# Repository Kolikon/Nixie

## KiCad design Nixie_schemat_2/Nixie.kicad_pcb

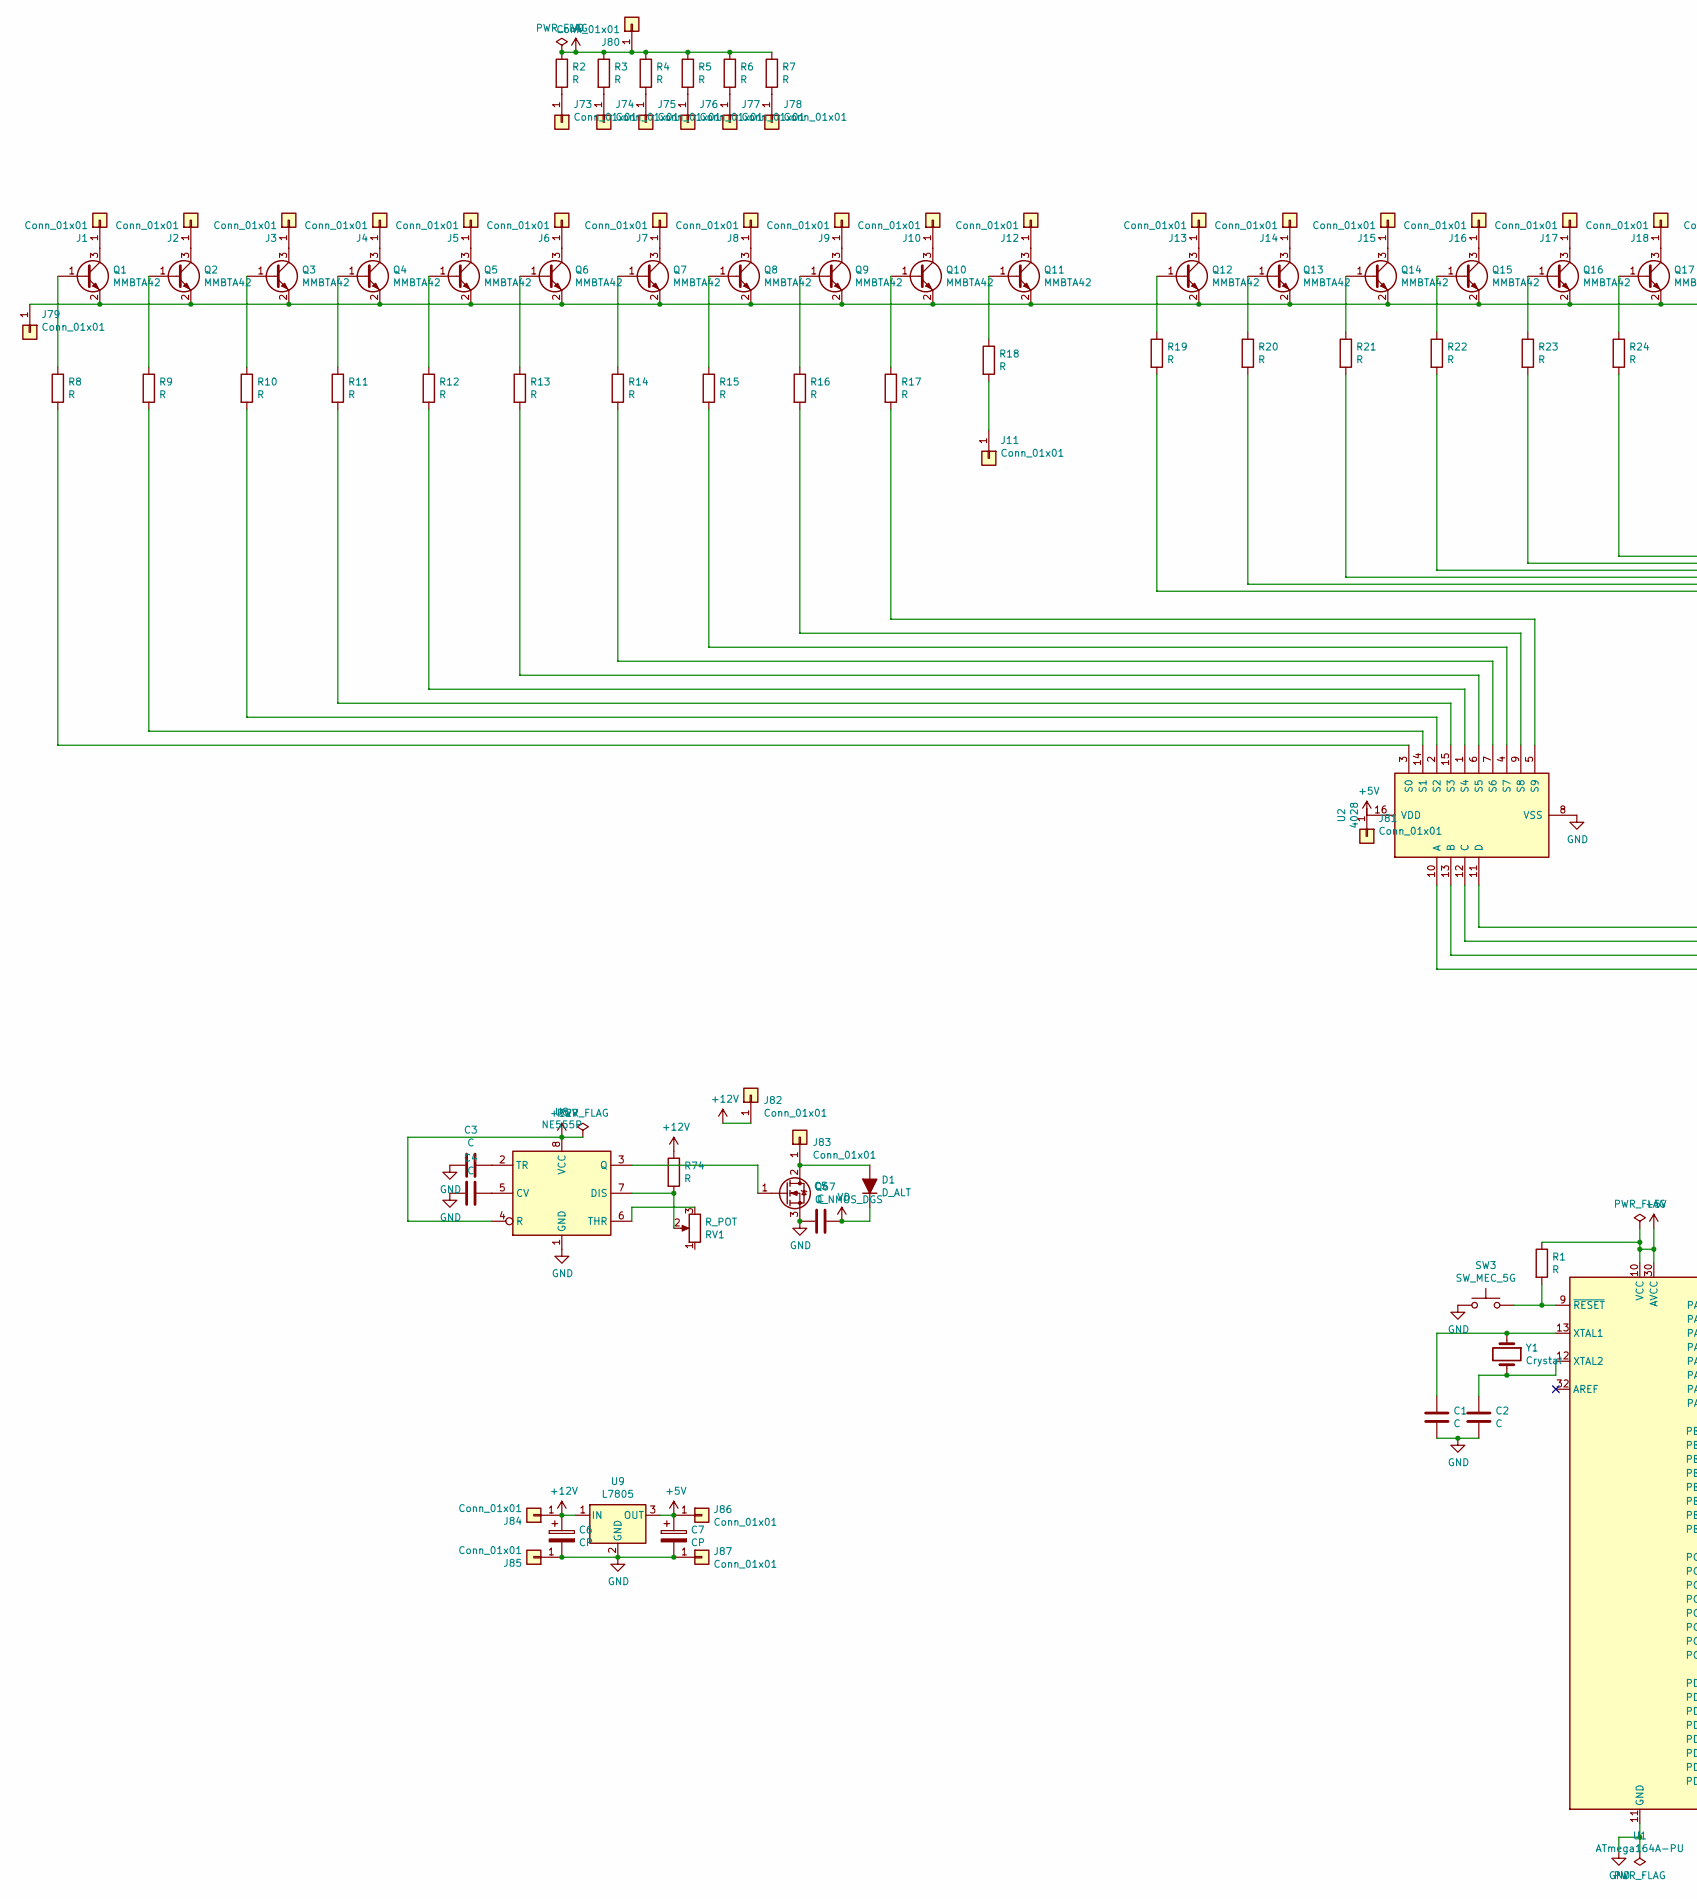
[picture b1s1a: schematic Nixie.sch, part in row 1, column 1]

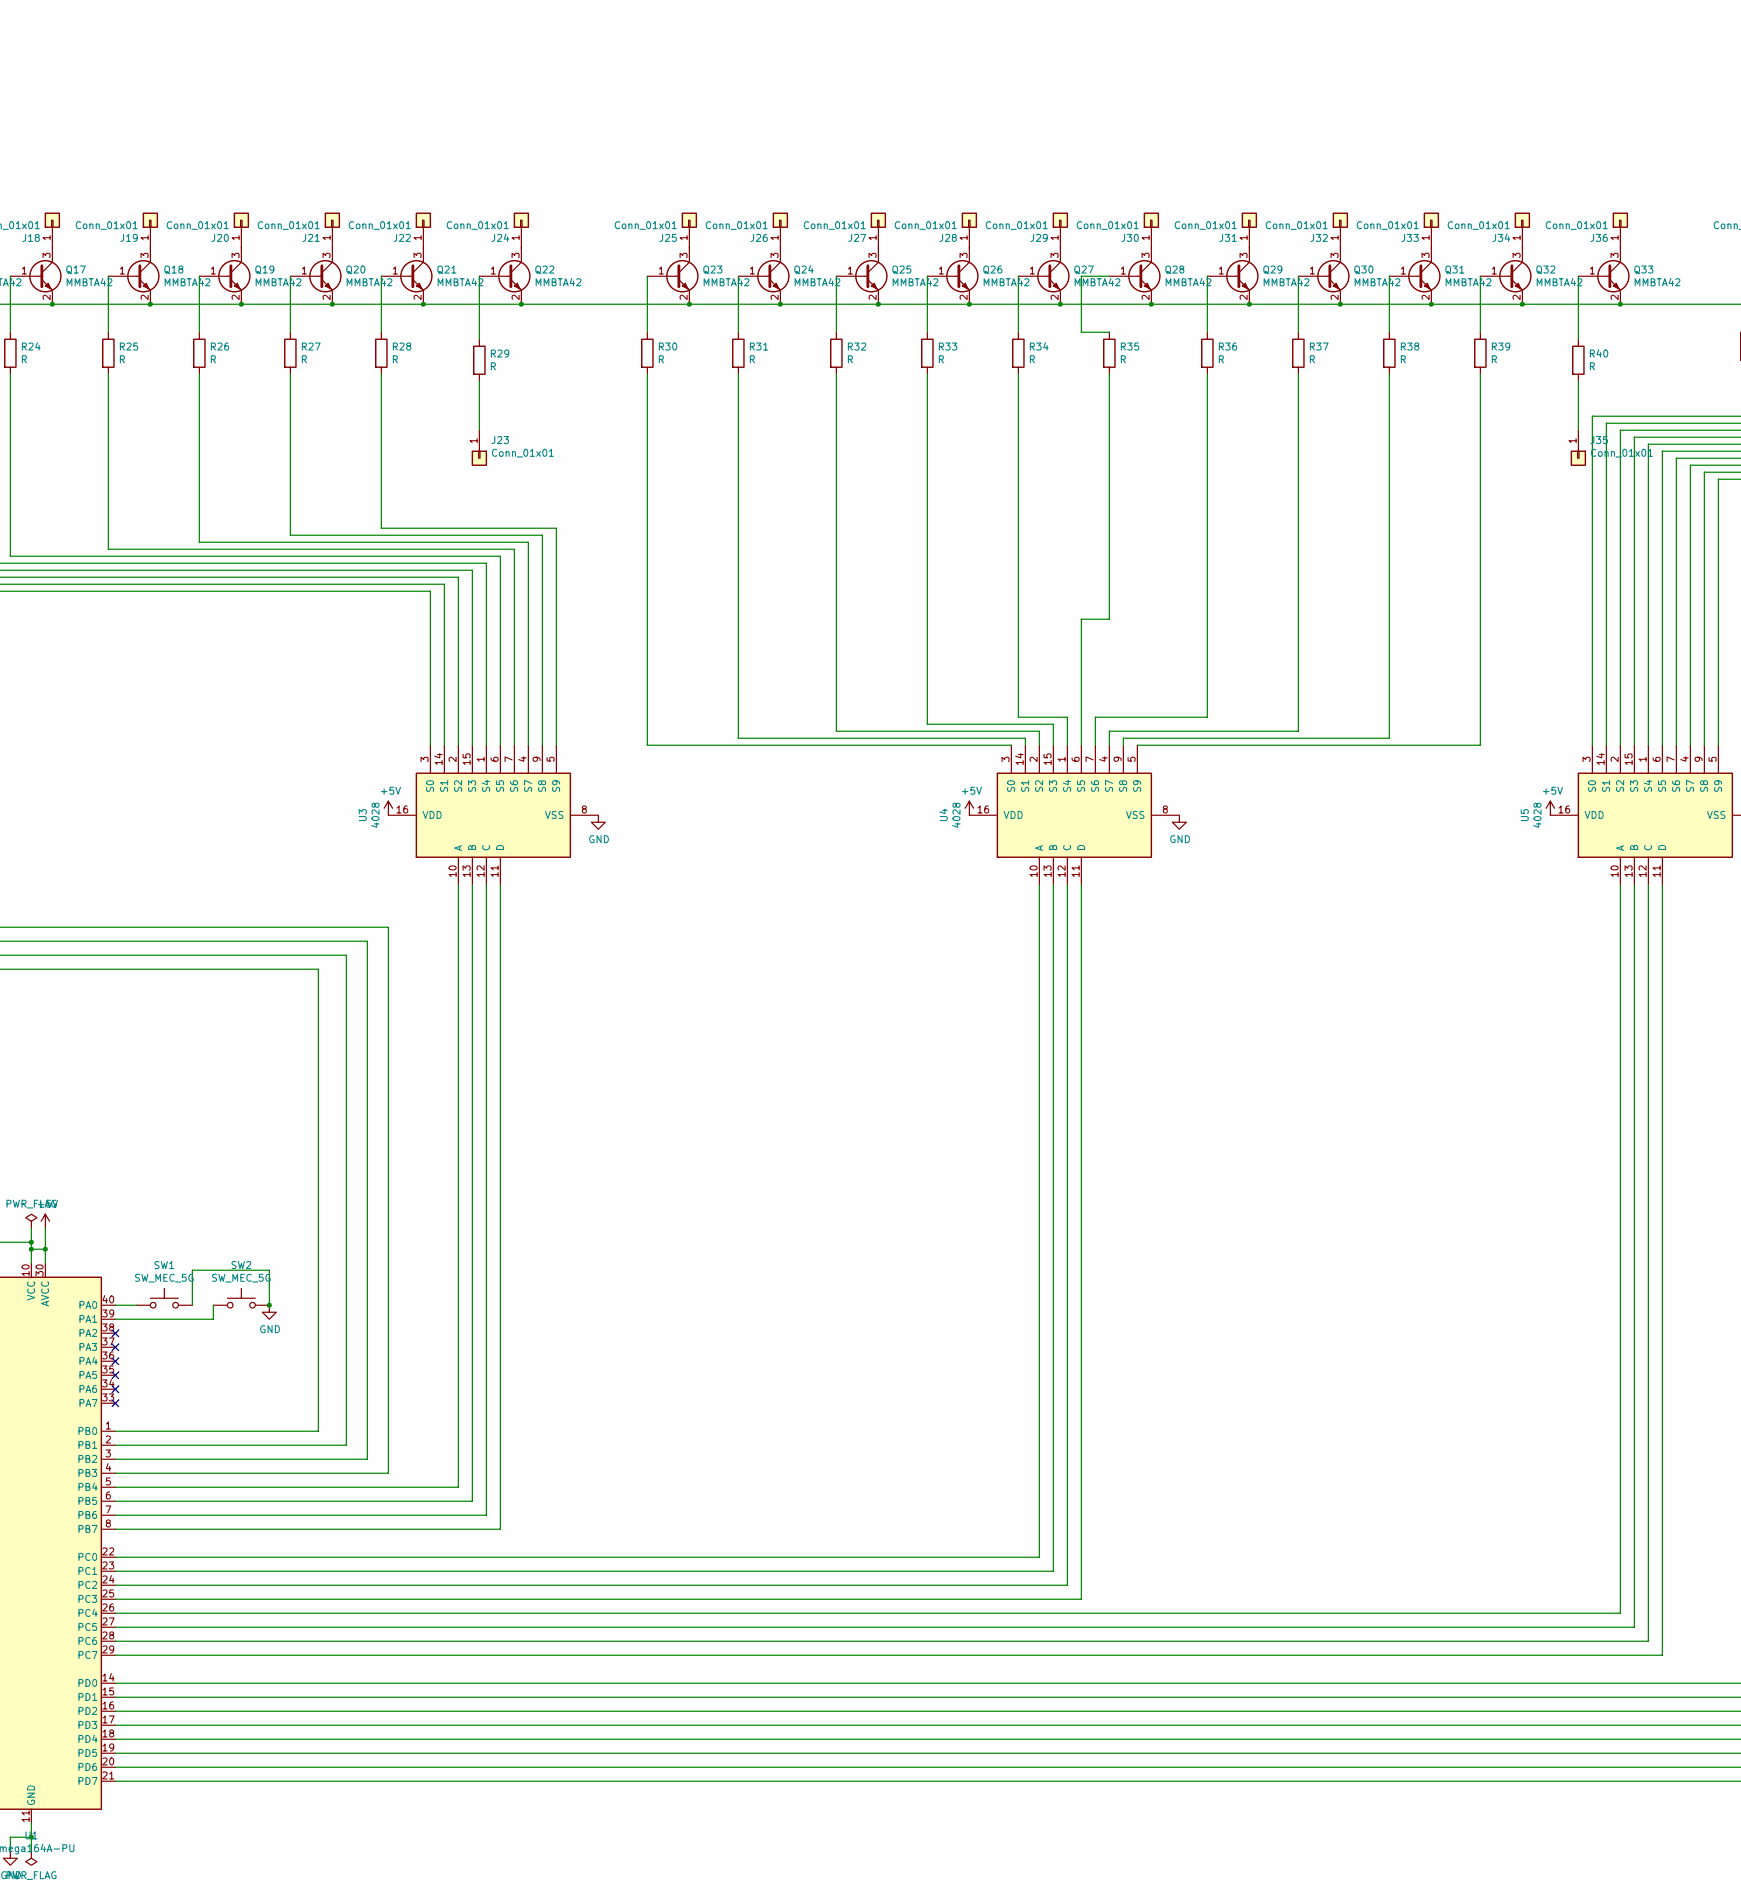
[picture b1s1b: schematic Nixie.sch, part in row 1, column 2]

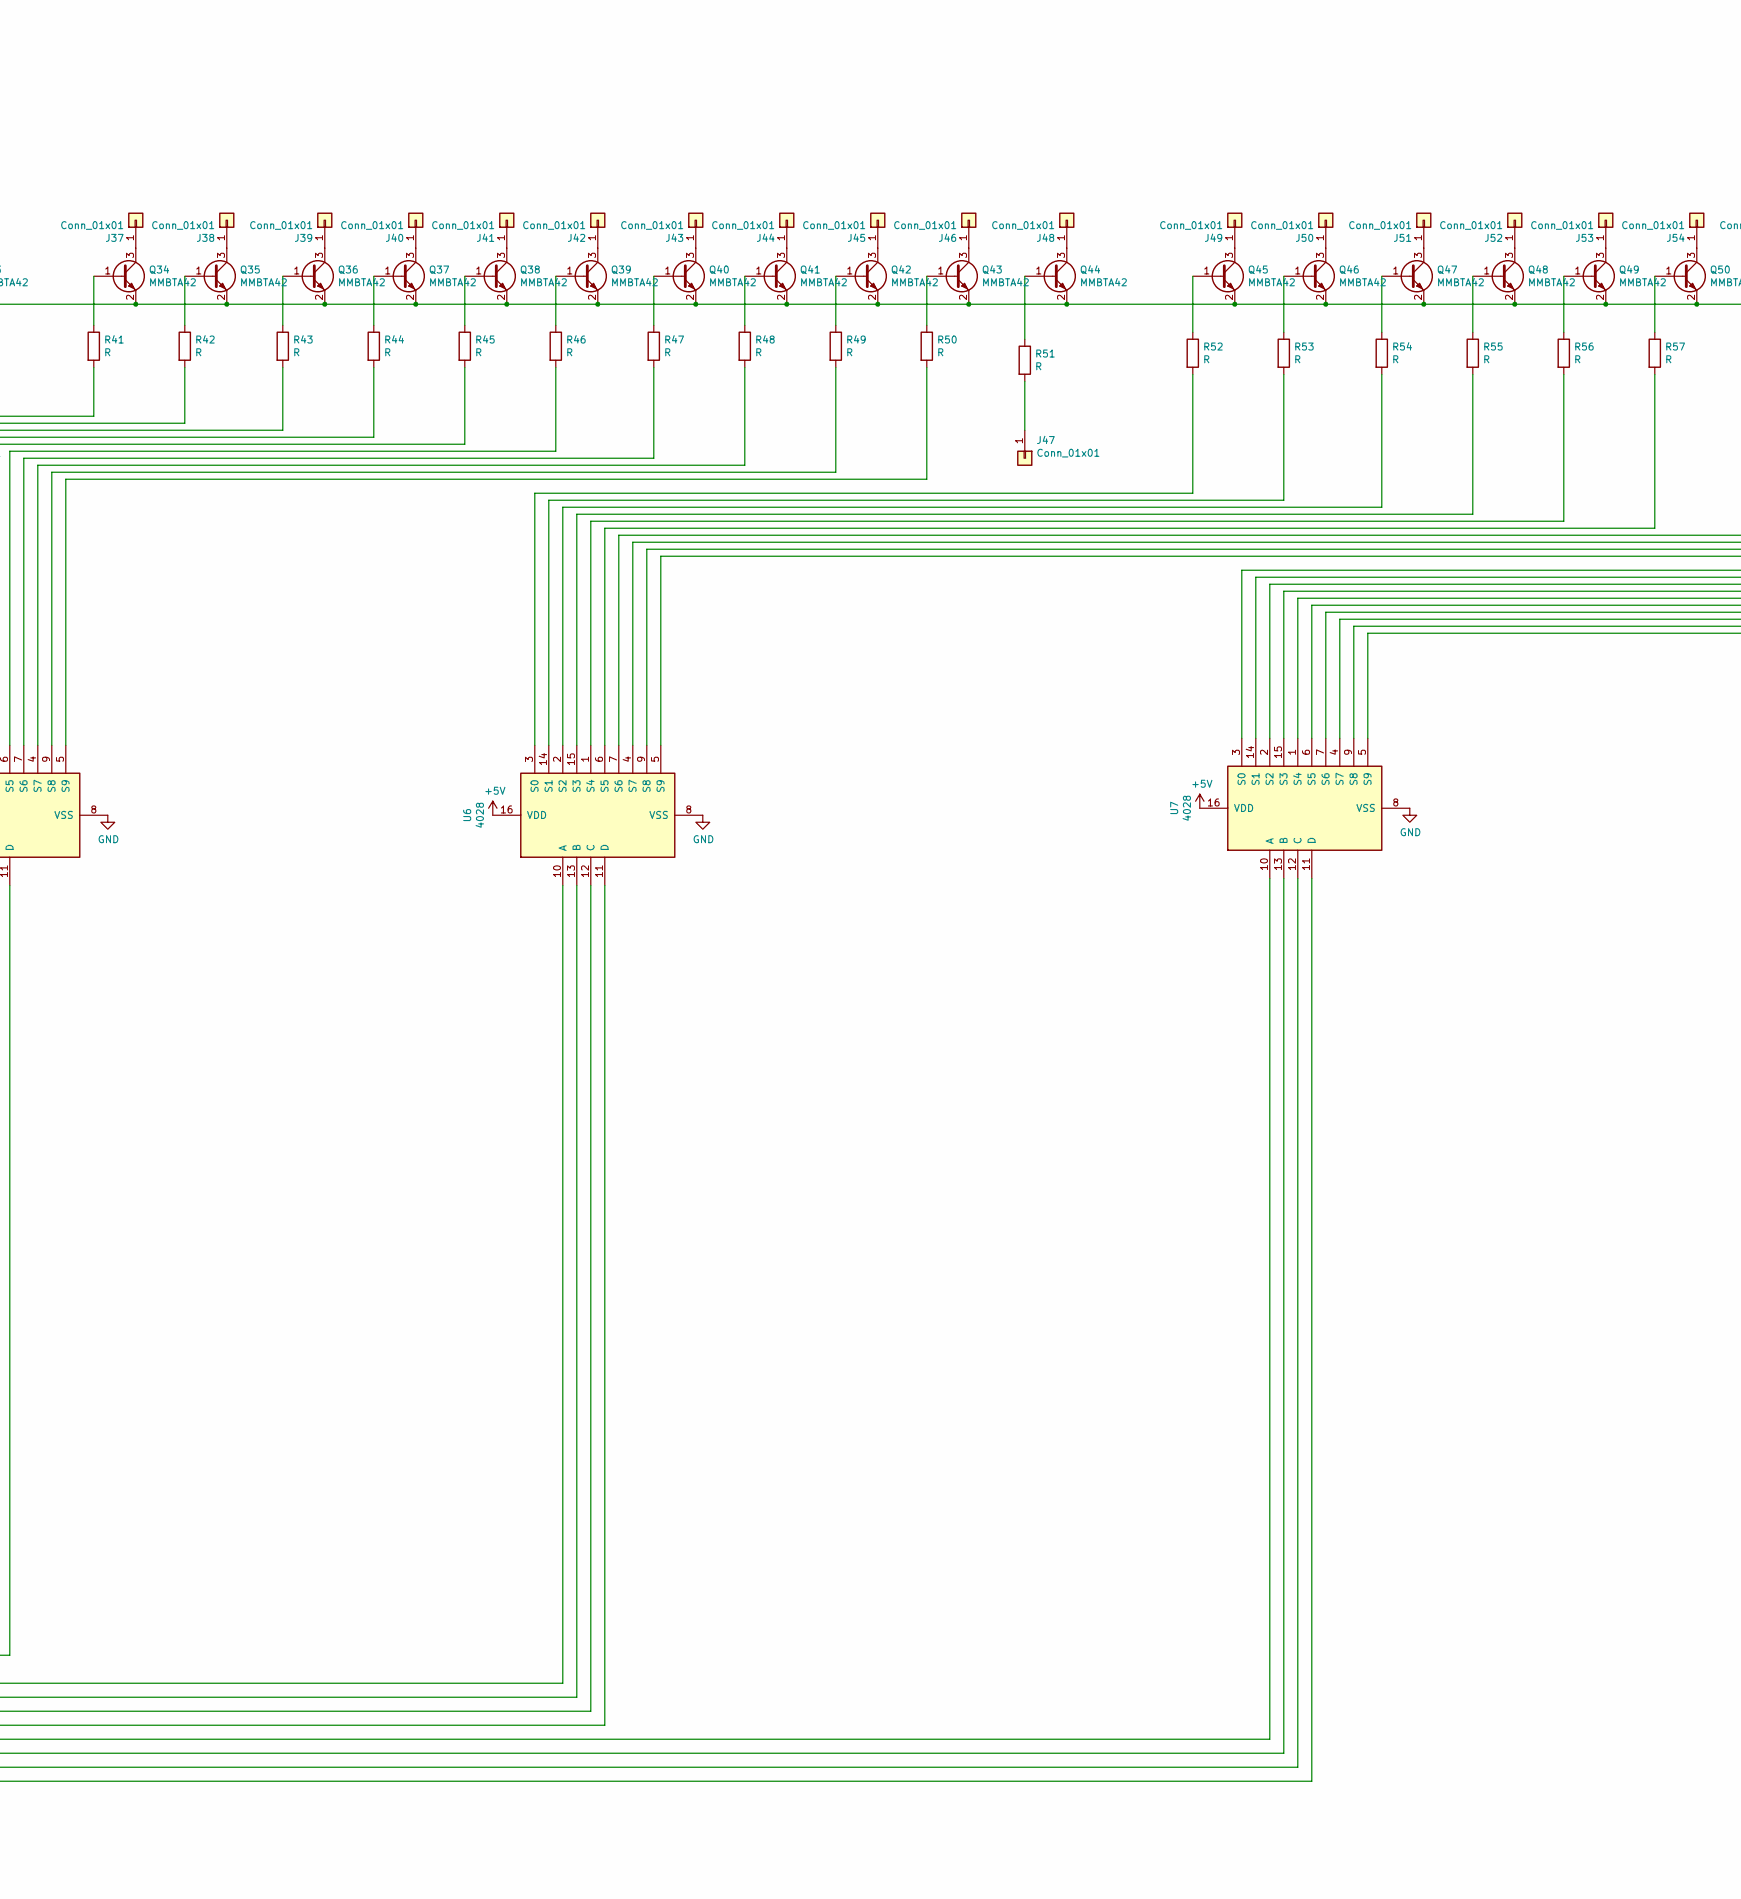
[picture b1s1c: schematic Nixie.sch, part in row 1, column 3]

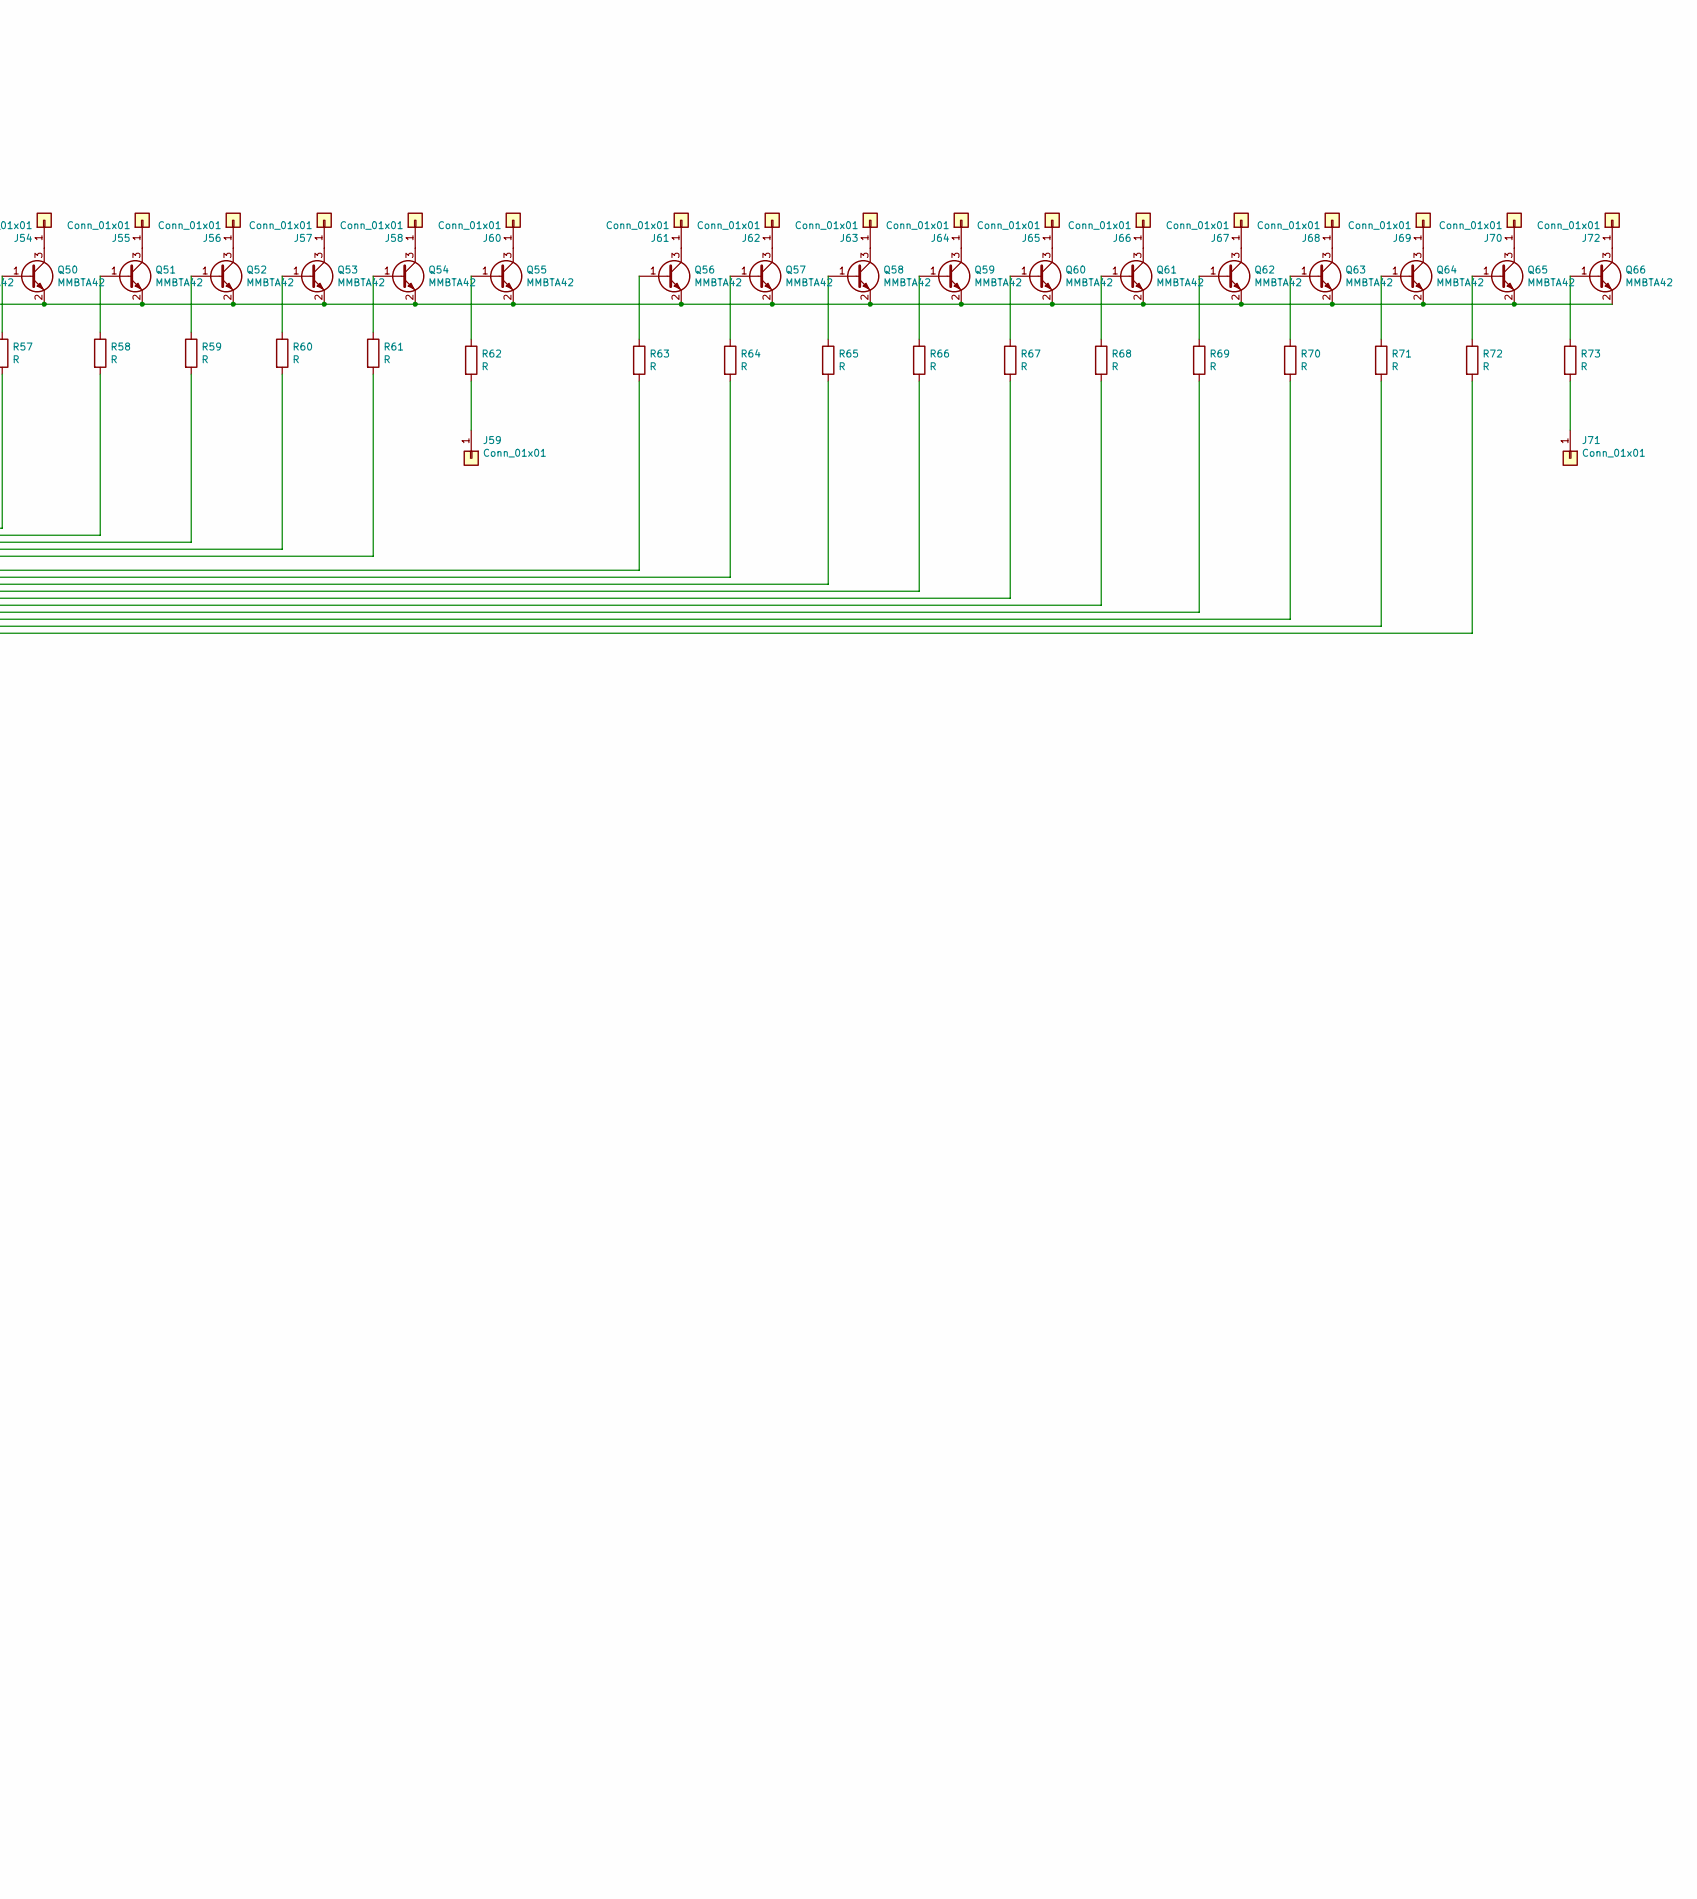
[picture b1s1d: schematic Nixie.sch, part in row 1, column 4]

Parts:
C1, C2: C; C_Disc_D3.0mm_W1.6mm_P2.50mm
C3: C; C_Disc_D4.3mm_W1.9mm_P5.00mm
C4: C; C_Disc_D4.7mm_W2.5mm_P5.00mm
C5: C; C_Rect_L18.0mm_W5.0mm_P15.00mm_FKS3_FKP3
C6, C7: CP; CP_Radial_D10.0mm_P5.00mm
D1: D_ALT; D_DO-41_SOD81_P10.16mm_Horizontal
J1, J2, J3, J4, J5, J6, J7, J8, J9, J10, J11, J12, J13, J14, J15, J16, J17, J18, J19, J20, J21, J22, J23, J24, J25, J26, J27, J28, J29, J30, J31, J32, J33, J34, J35, J36, J37, J38, J39, J40, J41, J42, J43, J44, J45, J46, J47, J48, J49, J50, J51, J52, J53, J54, J55, J56, J57, J58, J59, J60, J61, J62, J63, J64, J65, J66, J67, J68, J69, J70, J71, J72, J73, J74, J75, J76, J77, J78, J79, J80, J81, J82, J83, J84, J85, J86, J87: Conn_01x01; SolderWire-0.25sqmm_1x01_D0.65mm_OD2mm
Q1, Q2, Q3, Q4, Q5, Q6, Q7, Q8, Q9, Q10, Q11, Q12, Q13, Q14, Q15, Q16, Q17, Q18, Q19, Q20, Q21, Q22, Q23, Q24, Q25, Q26, Q27, Q28, Q29, Q30, Q31, Q32, Q33, Q34, Q35, Q36, Q37, Q38, Q39, Q40, Q41, Q42, Q43, Q44, Q45, Q46, Q47, Q48, Q49, Q50, Q51, Q52, Q53, Q54, Q55, Q56, Q57, Q58, Q59, Q60, Q61, Q62, Q63, Q64, Q65, Q66: MMBTA42; SOT-23(szerszy)
Q67: Q_NMOS_DGS; TO-252-2
R1: R; R_Axial_DIN0204_L3.6mm_D1.6mm_P7.62mm_Horizontal
R2, R3, R4, R5, R6, R7, R74: R; R_Axial_DIN0207_L6.3mm_D2.5mm_P10.16mm_Horizontal
R8, R9, R10, R11, R12, R13, R14, R15, R16, R17, R18, R19, R20, R21, R22, R23, R24, R25, R26, R27, R28, R29, R30, R31, R32, R33, R34, R35, R36, R37, R38, R39, R40, R41, R42, R43, R44, R45, R46, R47, R48, R49, R50, R51, R52, R53, R54, R55, R56, R57, R58, R59, R60, R61, R62, R63, R64, R65, R66, R67, R68, R69, R70, R71, R72, R73: R; R_1206_3216Metric
RV1: R_POT; Potentiometer_Piher_PT-6-V_Vertical
SW1, SW2, SW3: SW_MEC_5G; SW_PUSH_6mm
U1: ATmega164A-PU; DIP-40_W15.24mm_Socket
U2, U3, U4, U5, U6, U7: 4028; SO-16_5.3x10.2mm_P1.27mm
U8: NE555P; DIP-8_W7.62mm
U9: L7805; TO-263-2
Y1: Crystal; Crystal_HC49-4H_Vertical

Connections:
+5V: C7.1, J81.1, J86.1, R1.1, U1.10 (VCC), U1.30 (AVCC), U2.16 (VDD), U3.16 (VDD), U4.16 (VDD), U5.16 (VDD), U6.16 (VDD), U7.16 (VDD), U9.3 (OUT)
+12V: C6.1, J82.1, J84.1, R74.1, U8.4 (R), U8.8 (VCC), U9.1 (IN)
unnamed: C1.1, U1.13 (XTAL1), Y1.1
unnamed: C2.1, U1.12 (XTAL2), Y1.2
unnamed: C4.1, U8.5 (CV)
unnamed: D1.2 (A), J83.1, Q67.2 (D)
unnamed: J1.1, Q1.3 (C)
unnamed: J2.1, Q2.3 (C)
unnamed: J3.1, Q3.3 (C)
unnamed: J4.1, Q4.3 (C)
unnamed: J5.1, Q5.3 (C)
unnamed: J6.1, Q6.3 (C)
unnamed: J7.1, Q7.3 (C)
unnamed: J8.1, Q8.3 (C)
unnamed: J9.1, Q9.3 (C)
unnamed: J10.1, Q10.3 (C)
unnamed: J11.1, R18.2
unnamed: J12.1, Q11.3 (C)
unnamed: J13.1, Q12.3 (C)
unnamed: J14.1, Q13.3 (C)
unnamed: J15.1, Q14.3 (C)
unnamed: J16.1, Q15.3 (C)
unnamed: J17.1, Q16.3 (C)
unnamed: J18.1, Q17.3 (C)
unnamed: J19.1, Q18.3 (C)
unnamed: J20.1, Q19.3 (C)
unnamed: J21.1, Q20.3 (C)
unnamed: J22.1, Q21.3 (C)
unnamed: J23.1, R29.2
unnamed: J24.1, Q22.3 (C)
unnamed: J25.1, Q23.3 (C)
unnamed: J26.1, Q24.3 (C)
unnamed: J27.1, Q25.3 (C)
unnamed: J28.1, Q26.3 (C)
unnamed: J29.1, Q27.3 (C)
unnamed: J30.1, Q28.3 (C)
unnamed: J31.1, Q29.3 (C)
unnamed: J32.1, Q30.3 (C)
unnamed: J33.1, Q31.3 (C)
unnamed: J34.1, Q32.3 (C)
unnamed: J35.1, R40.2
unnamed: J36.1, Q33.3 (C)
unnamed: J37.1, Q34.3 (C)
unnamed: J38.1, Q35.3 (C)
unnamed: J39.1, Q36.3 (C)
unnamed: J40.1, Q37.3 (C)
unnamed: J41.1, Q38.3 (C)
unnamed: J42.1, Q39.3 (C)
unnamed: J43.1, Q40.3 (C)
unnamed: J44.1, Q41.3 (C)
unnamed: J45.1, Q42.3 (C)
unnamed: J46.1, Q43.3 (C)
unnamed: J47.1, R51.2
unnamed: J48.1, Q44.3 (C)
unnamed: J49.1, Q45.3 (C)
unnamed: J50.1, Q46.3 (C)
unnamed: J51.1, Q47.3 (C)
unnamed: J52.1, Q48.3 (C)
unnamed: J53.1, Q49.3 (C)
unnamed: J54.1, Q50.3 (C)
unnamed: J55.1, Q51.3 (C)
unnamed: J56.1, Q52.3 (C)
unnamed: J57.1, Q53.3 (C)
unnamed: J58.1, Q54.3 (C)
unnamed: J59.1, R62.2
unnamed: J60.1, Q55.3 (C)
unnamed: J61.1, Q56.3 (C)
unnamed: J62.1, Q57.3 (C)
unnamed: J63.1, Q58.3 (C)
unnamed: J64.1, Q59.3 (C)
unnamed: J65.1, Q60.3 (C)
unnamed: J66.1, Q61.3 (C)
unnamed: J67.1, Q62.3 (C)
unnamed: J68.1, Q63.3 (C)
unnamed: J69.1, Q64.3 (C)
unnamed: J70.1, Q65.3 (C)
unnamed: J71.1, R73.2
unnamed: J72.1, Q66.3 (C)
unnamed: J73.1, R2.2
unnamed: J74.1, R3.2
unnamed: J75.1, R4.2
unnamed: J76.1, R5.2
unnamed: J77.1, R6.2
unnamed: J78.1, R7.2
unnamed: Q1.1 (B), R8.1
unnamed: Q2.1 (B), R9.1
unnamed: Q3.1 (B), R10.1
unnamed: Q4.1 (B), R11.1
unnamed: Q5.1 (B), R12.1
unnamed: Q6.1 (B), R13.1
unnamed: Q7.1 (B), R14.1
unnamed: Q8.1 (B), R15.1
unnamed: Q9.1 (B), R16.1
unnamed: Q10.1 (B), R17.1
unnamed: Q11.1 (B), R18.1
unnamed: Q12.1 (B), R19.1
unnamed: Q13.1 (B), R20.1
unnamed: Q14.1 (B), R21.1
unnamed: Q15.1 (B), R22.1
unnamed: Q16.1 (B), R23.1
unnamed: Q17.1 (B), R24.1
unnamed: Q18.1 (B), R25.1
unnamed: Q19.1 (B), R26.1
unnamed: Q20.1 (B), R27.1
unnamed: Q21.1 (B), R28.1
unnamed: Q22.1 (B), R29.1
unnamed: Q23.1 (B), R30.1
unnamed: Q24.1 (B), R31.1
unnamed: Q25.1 (B), R32.1
unnamed: Q26.1 (B), R33.1
unnamed: Q27.1 (B), R34.1
unnamed: Q28.1 (B), R35.1
unnamed: Q29.1 (B), R36.1
unnamed: Q30.1 (B), R37.1
unnamed: Q31.1 (B), R38.1
unnamed: Q32.1 (B), R39.1
unnamed: Q33.1 (B), R40.1
unnamed: Q34.1 (B), R41.1
unnamed: Q35.1 (B), R42.1
unnamed: Q36.1 (B), R43.1
unnamed: Q37.1 (B), R44.1
unnamed: Q38.1 (B), R45.1
unnamed: Q39.1 (B), R46.1
unnamed: Q40.1 (B), R47.1
unnamed: Q41.1 (B), R48.1
unnamed: Q42.1 (B), R49.1
unnamed: Q43.1 (B), R50.1
unnamed: Q44.1 (B), R51.1
unnamed: Q45.1 (B), R52.1
unnamed: Q46.1 (B), R53.1
unnamed: Q47.1 (B), R54.1
unnamed: Q48.1 (B), R55.1
unnamed: Q49.1 (B), R56.1
unnamed: Q50.1 (B), R57.1
unnamed: Q51.1 (B), R58.1
unnamed: Q52.1 (B), R59.1
unnamed: Q53.1 (B), R60.1
unnamed: Q54.1 (B), R61.1
unnamed: Q55.1 (B), R62.1
unnamed: Q56.1 (B), R63.1
unnamed: Q57.1 (B), R64.1
unnamed: Q58.1 (B), R65.1
unnamed: Q59.1 (B), R66.1
unnamed: Q60.1 (B), R67.1
unnamed: Q61.1 (B), R68.1
unnamed: Q62.1 (B), R69.1
unnamed: Q63.1 (B), R70.1
unnamed: Q64.1 (B), R71.1
unnamed: Q65.1 (B), R72.1
unnamed: Q66.1 (B), R73.1
unnamed: Q67.1 (G), U8.3 (Q)
unnamed: R8.2, U2.3 (S0)
unnamed: R9.2, U2.14 (S1)
unnamed: R10.2, U2.2 (S2)
unnamed: R11.2, U2.15 (S3)
unnamed: R12.2, U2.1 (S4)
unnamed: R13.2, U2.6 (S5)
unnamed: R14.2, U2.7 (S6)
unnamed: R15.2, U2.4 (S7)
unnamed: R16.2, U2.9 (S8)
unnamed: R17.2, U2.5 (S9)
unnamed: R19.2, U3.3 (S0)
unnamed: R20.2, U3.14 (S1)
unnamed: R21.2, U3.2 (S2)
unnamed: R22.2, U3.15 (S3)
unnamed: R23.2, U3.1 (S4)
unnamed: R24.2, U3.6 (S5)
unnamed: R25.2, U3.7 (S6)
unnamed: R26.2, U3.4 (S7)
unnamed: R27.2, U3.9 (S8)
unnamed: R28.2, U3.5 (S9)
unnamed: R30.2, U4.3 (S0)
unnamed: R31.2, U4.14 (S1)
unnamed: R32.2, U4.2 (S2)
unnamed: R33.2, U4.15 (S3)
unnamed: R34.2, U4.1 (S4)
unnamed: R35.2, U4.6 (S5)
unnamed: R36.2, U4.7 (S6)
unnamed: R37.2, U4.4 (S7)
unnamed: R38.2, U4.9 (S8)
unnamed: R39.2, U4.5 (S9)
unnamed: R41.2, U5.3 (S0)
unnamed: R42.2, U5.14 (S1)
unnamed: R43.2, U5.2 (S2)
unnamed: R44.2, U5.15 (S3)
unnamed: R45.2, U5.1 (S4)
unnamed: R46.2, U5.6 (S5)
unnamed: R47.2, U5.7 (S6)
unnamed: R48.2, U5.4 (S7)
unnamed: R49.2, U5.9 (S8)
unnamed: R50.2, U5.5 (S9)
unnamed: R52.2, U6.3 (S0)
unnamed: R53.2, U6.14 (S1)
unnamed: R54.2, U6.2 (S2)
unnamed: R55.2, U6.15 (S3)
unnamed: R56.2, U6.1 (S4)
unnamed: R57.2, U6.6 (S5)
unnamed: R58.2, U6.7 (S6)
unnamed: R59.2, U6.4 (S7)
unnamed: R60.2, U6.9 (S8)
unnamed: R61.2, U6.5 (S9)
unnamed: R63.2, U7.3 (S0)
unnamed: R64.2, U7.14 (S1)
unnamed: R65.2, U7.2 (S2)
unnamed: R66.2, U7.15 (S3)
unnamed: R67.2, U7.1 (S4)
unnamed: R68.2, U7.6 (S5)
unnamed: R69.2, U7.7 (S6)
unnamed: R70.2, U7.4 (S7)
unnamed: R71.2, U7.9 (S8)
unnamed: R72.2, U7.5 (S9)
unnamed: R74.2, RV1.2, U8.7 (DIS)
unnamed: U1.1 (PB0), U2.10 (A)
unnamed: U1.2 (PB1), U2.13 (B)
unnamed: U1.3 (PB2), U2.12 (C)
unnamed: U1.4 (PB3), U2.11 (D)
unnamed: U1.5 (PB4), U3.10 (A)
unnamed: U1.6 (PB5), U3.13 (B)
unnamed: U1.7 (PB6), U3.12 (C)
unnamed: U1.8 (PB7), U3.11 (D)
unnamed: U1.14 (PD0), U6.10 (A)
unnamed: U1.15 (PD1), U6.13 (B)
unnamed: U1.16 (PD2), U6.12 (C)
unnamed: U1.17 (PD3), U6.11 (D)
unnamed: U1.18 (PD4), U7.10 (A)
unnamed: U1.19 (PD5), U7.13 (B)
unnamed: U1.20 (PD6), U7.12 (C)
unnamed: U1.21 (PD7), U7.11 (D)
unnamed: U1.22 (PC0), U4.10 (A)
unnamed: U1.23 (PC1), U4.13 (B)
unnamed: U1.24 (PC2), U4.12 (C)
unnamed: U1.25 (PC3), U4.11 (D)
unnamed: U1.26 (PC4), U5.10 (A)
unnamed: U1.27 (PC5), U5.13 (B)
unnamed: U1.28 (PC6), U5.12 (C)
unnamed: U1.29 (PC7), U5.11 (D)
VD: C5.1, D1.1 (K), J80.1, R2.1, R3.1, R4.1, R5.1, R6.1, R7.1

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
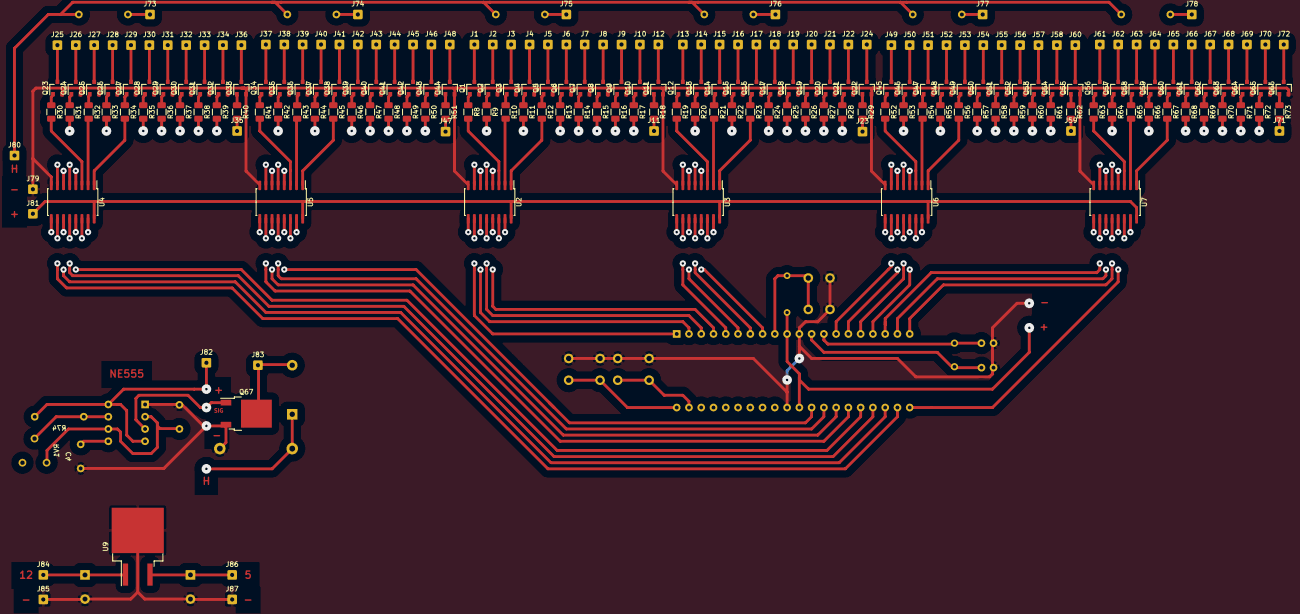
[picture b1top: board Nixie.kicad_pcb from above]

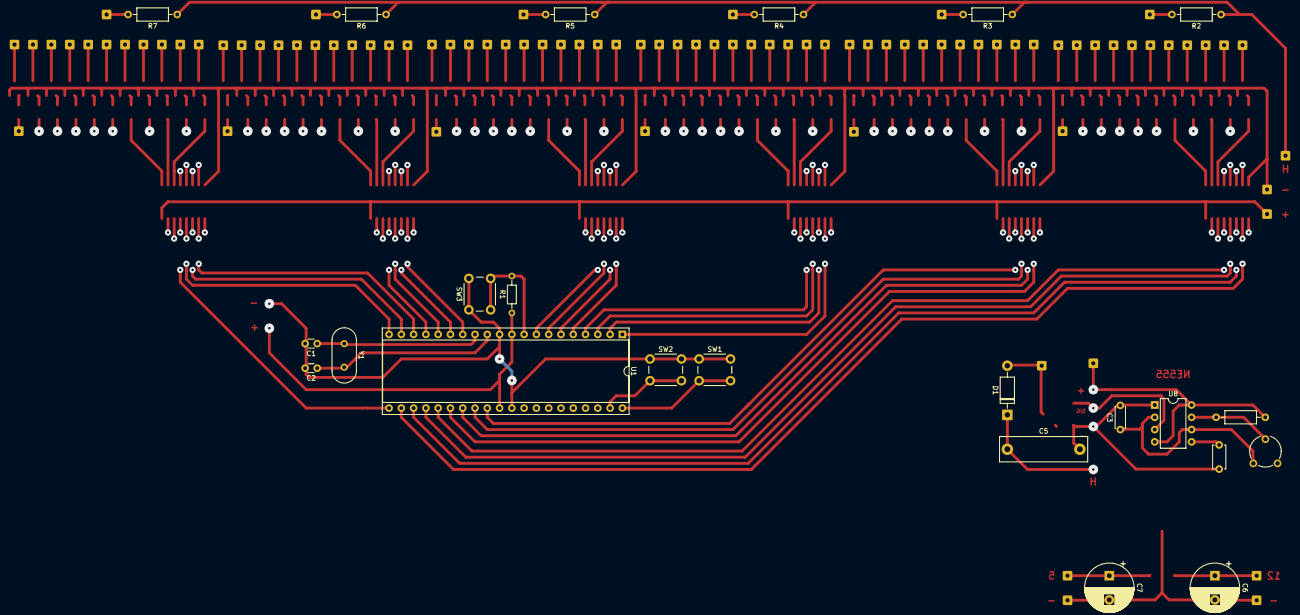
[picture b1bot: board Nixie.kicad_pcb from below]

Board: 2 copper layers, 250 parts (23 on the bottom side), 242 nets.
